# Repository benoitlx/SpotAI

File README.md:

# SpotAI

A powerfull Robot with embedded AI, Speech Recognition and so more

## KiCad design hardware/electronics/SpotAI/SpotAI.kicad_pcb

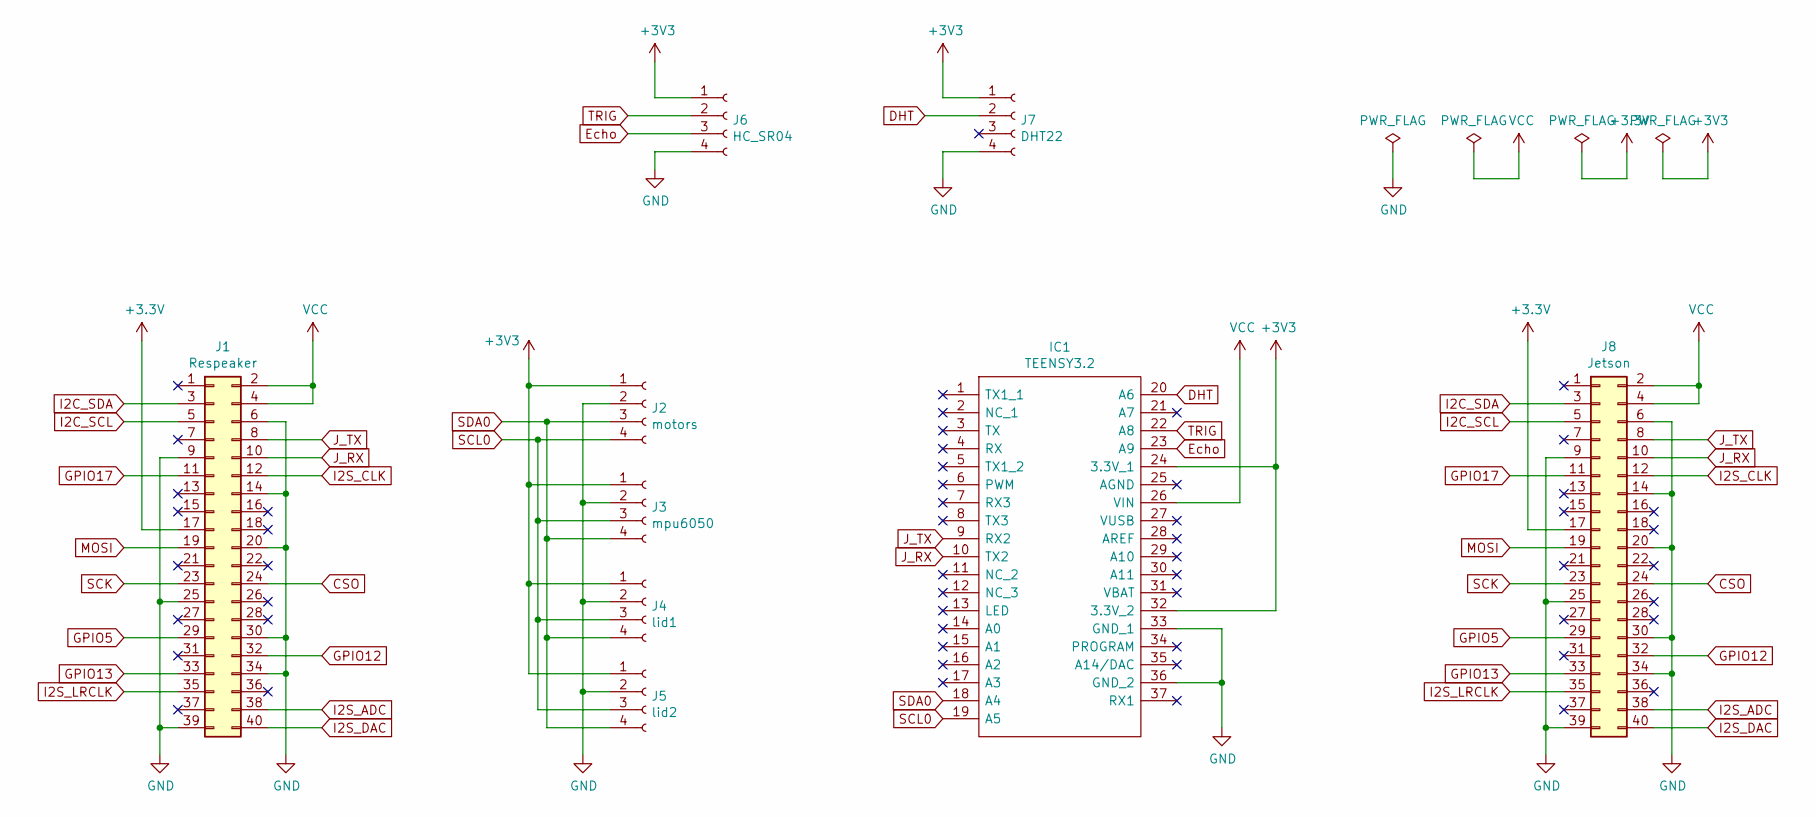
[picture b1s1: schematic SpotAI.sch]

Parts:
IC1: TEENSY3.2; TEENSY32; Manufacturer_Part_Number TEENSY3.2
J1: Respeaker; PinHeader_2x20_P2.54mm_Vertical
J2: motors; PinHeader_1x04_P2.54mm_Vertical
J3: mpu6050; PinHeader_1x04_P2.54mm_Vertical
J4: lid1; PinHeader_1x04_P2.54mm_Vertical
J5: lid2; PinHeader_1x04_P2.54mm_Vertical
J6: HC_SR04; PinHeader_1x04_P2.54mm_Vertical
J7: DHT22; PinHeader_1x04_P2.54mm_Vertical
J8: Jetson; PinHeader_2x20_P2.54mm_Vertical

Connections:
CSO: J1.24, J8.24
DHT: IC1.20 (A6), J7.2
Echo: IC1.23 (A9), J6.3
GND: IC1.33 (GND_1), IC1.36 (GND_2), J1.6, J1.9, J1.14, J1.20, J1.25, J1.30, J1.34, J1.39, J2.2, J3.2, J4.2, J5.2, J6.4, J7.4, J8.6, J8.9, J8.14, J8.20, J8.25, J8.30, J8.34, J8.39
GPIO5: J1.29, J8.29
GPIO12: J1.32, J8.32
GPIO13: J1.33, J8.33
GPIO17: J1.11, J8.11
I2C_SCL: J1.5, J8.5
I2C_SDA: J1.3, J8.3
I2S_ADC: J1.38, J8.38
I2S_CLK: J1.12, J8.12
I2S_DAC: J1.40, J8.40
I2S_LRCLK: J1.35, J8.35
J_RX: IC1.10 (TX2), J1.10, J8.10
J_TX: IC1.9 (RX2), J1.8, J8.8
MOSI: J1.19, J8.19
SCK: J1.23, J8.23
SCL0: IC1.19 (A5), J2.4, J3.3, J4.3, J5.3
SDA0: IC1.18 (A4), J2.3, J3.4, J4.4, J5.4
TRIG: IC1.22 (A8), J6.2
VCC: IC1.26 (VIN), J1.2, J1.4, J8.2, J8.4

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
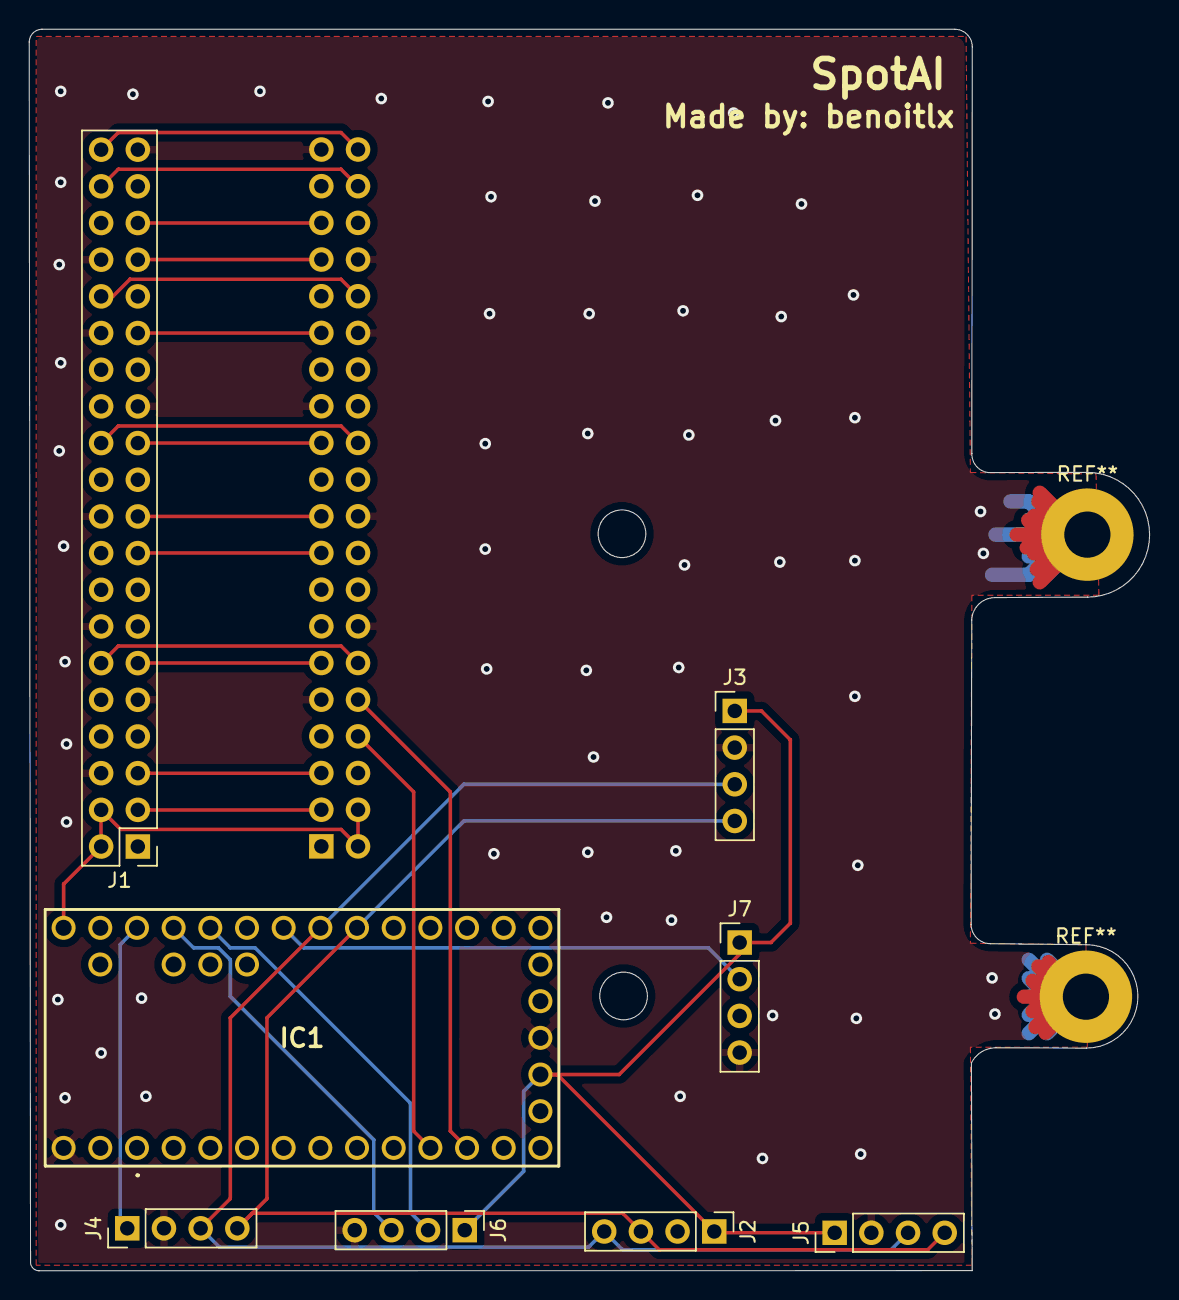
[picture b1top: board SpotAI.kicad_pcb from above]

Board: 2 copper layers, 77.6 x 86.0 mm, 9 parts (1 on the bottom side), 23 nets.

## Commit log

2021-07-11 test
2021-07-27 schematic
2021-07-27 pcb_edge_cut
2021-07-27 pcb_placement
2021-07-27 pcb_root;gerber
2021-07-29 platformio setup
2021-08-03 lidar and gyroscope
2021-08-03 README
2021-08-04 adding lidar
2021-08-05 2lidar and update function
2021-08-07 lib and files
2021-08-07 servos
2021-08-09 push
2021-08-10 servo interface
2021-08-10 change Angle type
2021-08-10 Serialization
